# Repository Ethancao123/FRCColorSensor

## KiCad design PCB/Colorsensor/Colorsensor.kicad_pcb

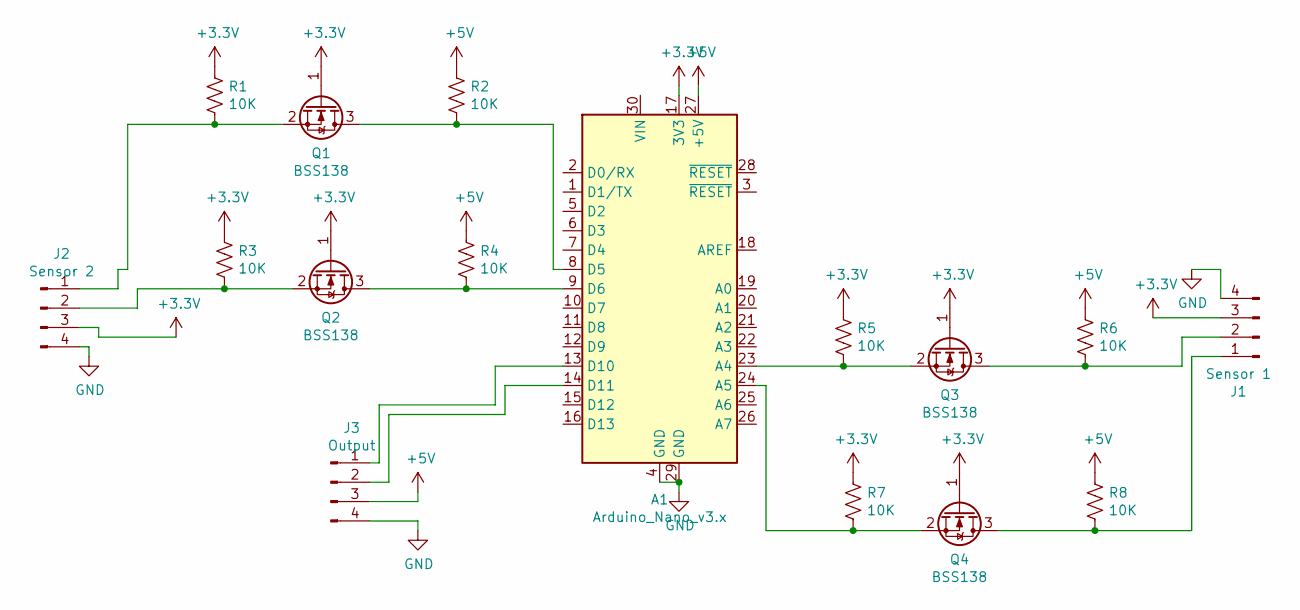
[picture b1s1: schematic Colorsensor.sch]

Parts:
A1: Arduino_Nano_v3.x; Arduino_Nano
J1: Sensor 1; JST_PH_S4B-PH-SM4-TB_1x04-1MP_P2.00mm_Horizontal
J2: Sensor 2; JST_PH_S4B-PH-SM4-TB_1x04-1MP_P2.00mm_Horizontal
J3: Output; JST_PH_S4B-PH-SM4-TB_1x04-1MP_P2.00mm_Horizontal
Q1, Q2, Q3, Q4: BSS138; SOT-23
R1, R2, R3, R4, R5, R6, R7, R8: 10K; R_1210_3225Metric

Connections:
+3V3: A1.17 (3V3), J1.3, J2.3, Q1.1 (G), Q2.1 (G), Q3.1 (G), Q4.1 (G), R1.1, R3.1, R5.1, R7.1
+5V: A1.27 (+5V), J3.3, R2.1, R4.1, R6.1, R8.1
GND: A1.4 (GND), A1.29 (GND), J1.4, J1.MP, J2.4, J2.MP, J3.4, J3.MP
unnamed: A1.8 (D5), Q1.3 (D), R2.2
unnamed: A1.9 (D6), Q2.3 (D), R4.2
unnamed: A1.13 (D10), J3.1
unnamed: A1.14 (D11), J3.2
unnamed: A1.23 (A4), Q3.2 (S), R5.2
unnamed: A1.24 (A5), Q4.2 (S), R7.2
unnamed: J1.1, Q4.3 (D), R8.2
unnamed: J1.2, Q3.3 (D), R6.2
unnamed: J2.1, Q1.2 (S), R1.2
unnamed: J2.2, Q2.2 (S), R3.2

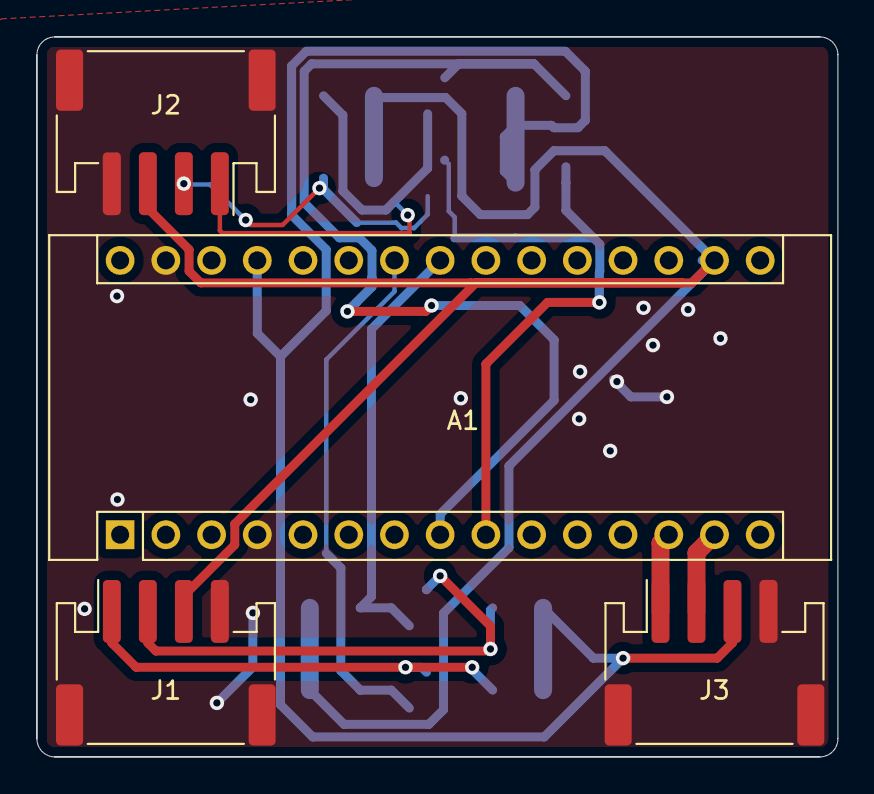
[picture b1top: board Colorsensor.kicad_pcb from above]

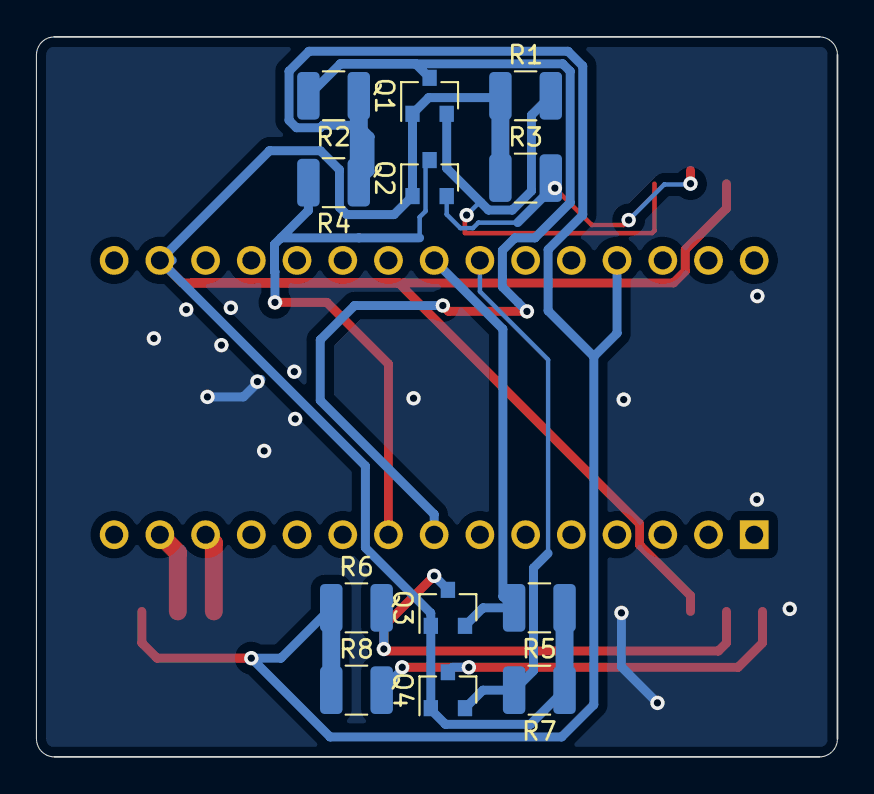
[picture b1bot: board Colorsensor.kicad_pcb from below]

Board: 2 copper layers, 44.5 x 40.0 mm, 16 parts (12 on the bottom side), 13 nets.

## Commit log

2022-02-17 chegnome
2022-02-17 still broke
2022-02-19 pogworks
2022-02-19 change i2c pins
